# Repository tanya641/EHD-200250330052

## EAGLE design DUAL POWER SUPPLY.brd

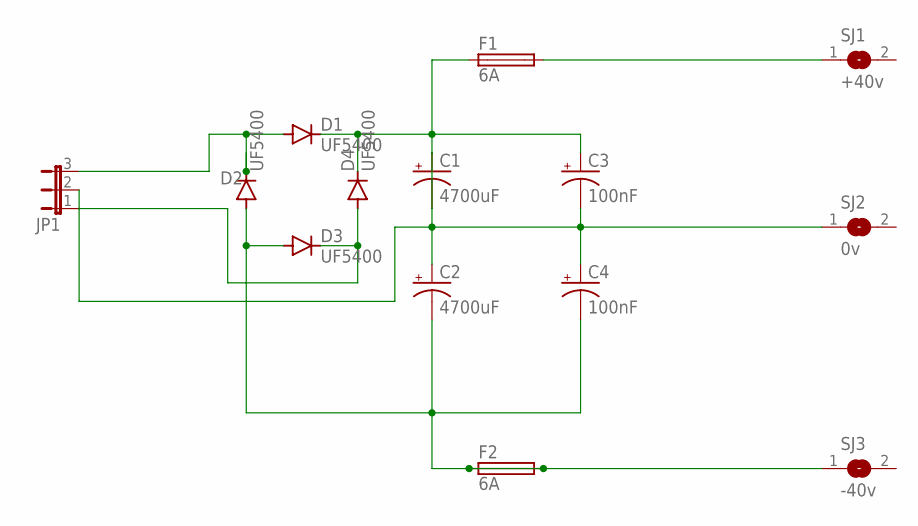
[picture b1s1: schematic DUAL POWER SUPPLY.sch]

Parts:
C1, C2: 4700uF; 175TMP-0808
C3, C4: 100nF; 175TMP-0808
D1, D2, D3, D4: UF5400; DO201-15
F1, F2: 6A; 19560
JP1: JP2W
SJ1: +40v; SJW
SJ2: 0v; SJW
SJ3: -40v; SJW

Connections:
unnamed: D1.A, D2.C, JP1.3
unnamed: C2.-, C4.-, D2.A, D3.A, F2.1, F2.2, SJ3.1
unnamed: F1.2, SJ1.1
unnamed: D3.C, D4.A, JP1.1
unnamed: C1.+, C1.-, C2.+, C3.+, C3.-, C4.+, D1.C, D4.C, F1.1, JP1.2, SJ2.1

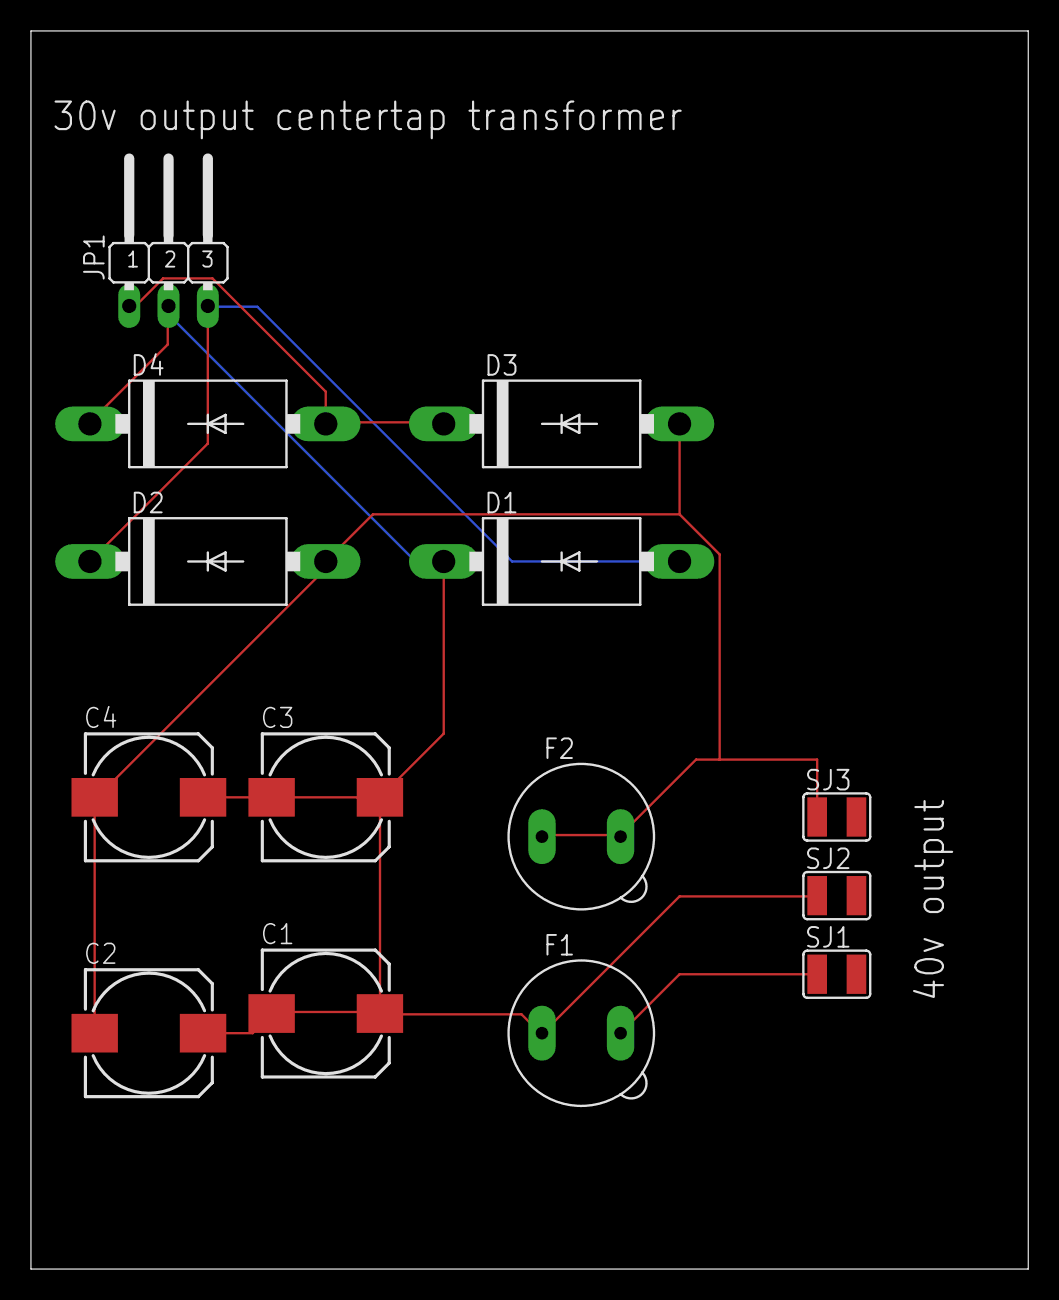
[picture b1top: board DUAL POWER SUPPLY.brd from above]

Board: 2 copper layers, 64.4 x 80.0 mm, 14 parts (0 on the bottom side), 5 nets.

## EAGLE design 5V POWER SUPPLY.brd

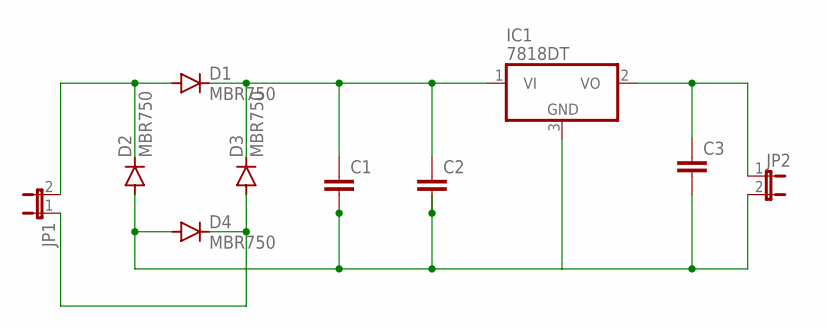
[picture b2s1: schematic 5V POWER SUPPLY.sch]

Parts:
C1, C2, C3: C22/6; C22.5B6
D1, D2, D3, D4: MBR750; TO220AC
IC1: 7818DT; TO252
JP1, JP2: JP1E; JP1

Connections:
unnamed: C1.2, C2.2, C3.2, D2.A, D4.A, IC1.3 (GND), JP2.2
unnamed: D3.A, D4.C, JP1.1
unnamed: D1.A, D2.C, JP1.2
unnamed: C1.1, C2.1, D1.C, D3.C, IC1.1 (VI)
unnamed: C3.1, IC1.2 (VO), JP2.1

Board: 2 copper layers, 10 parts (0 on the bottom side), 5 nets, no tracks yet.
